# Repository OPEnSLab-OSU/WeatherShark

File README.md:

# WeatherShark

Links via Fusion to CAD files to 3D print

Hanging rod: http://a360.co/2F3G7Bz

Crossbar: http://a360.co/2F3G7Bz

Bearing Hanger: http://a360.co/2EYjwWZ

Fiber Clamp: http://a360.co/2FCrSVv - the new version of this needs to be refined a bit to get a good latch on the fiber

Ventilator with Turbine Rod: http://a360.co/2EYo6IR

Body + Bottom Plate: http://a360.co/2EXwTed

Note: Currently missing in the documentation: the WeatherShark board should have a 100 kOhm resistor from the RTC INT Pin to VCC.

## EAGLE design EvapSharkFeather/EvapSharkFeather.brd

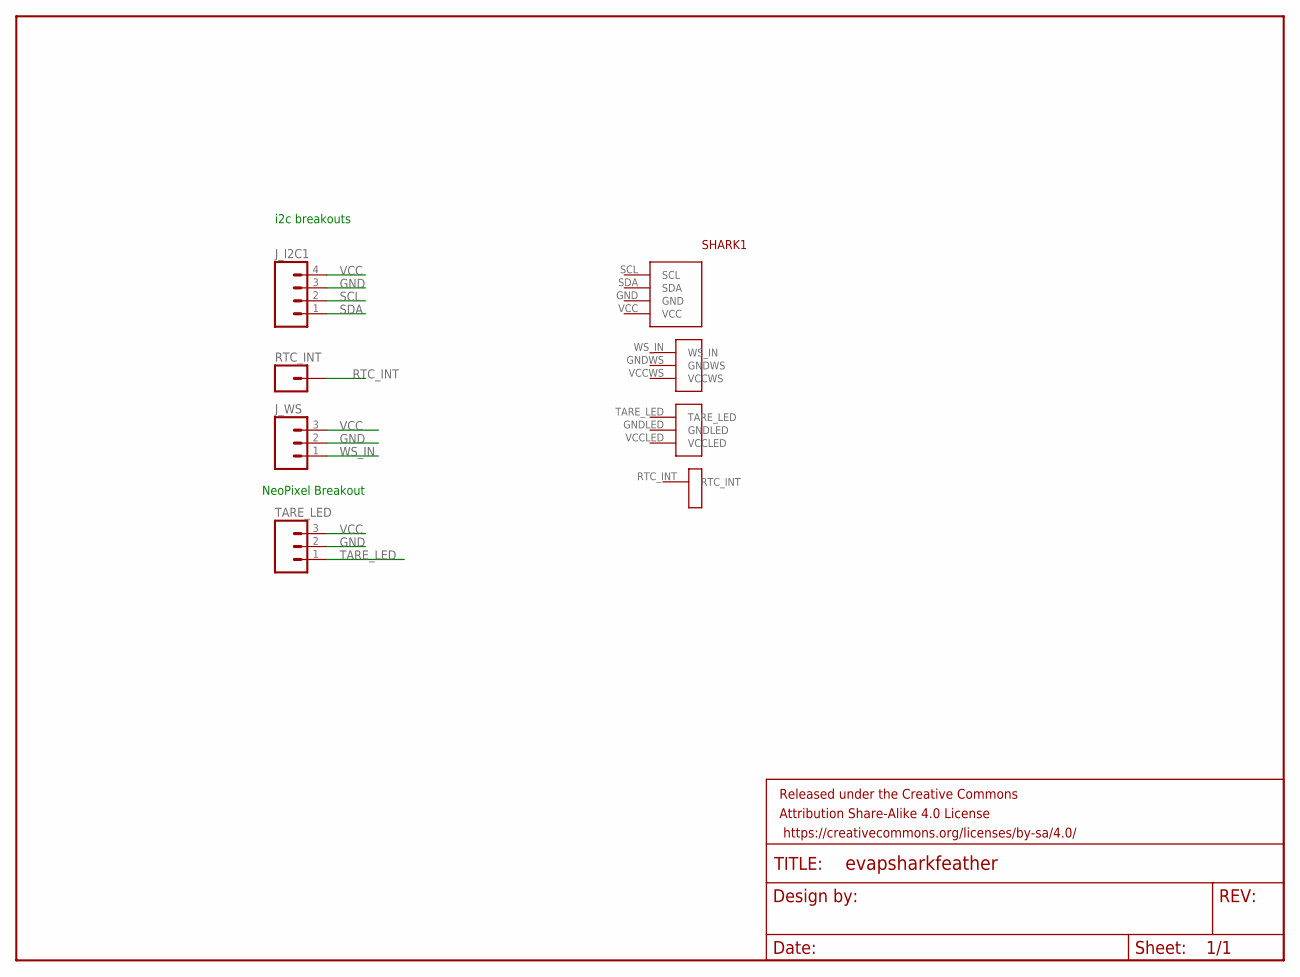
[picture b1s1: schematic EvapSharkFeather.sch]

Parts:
FRAME1: FRAME-LETTER; CREATIVE_COMMONS
J_I2C1: M04PTH; 1X04
J_WS: M03PTH; 1X03
RTC_INT: M01PTH; 1X01
SHARK1: EVAPSHARK
TARE_LED: M03PTH; 1X03

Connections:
GND: J_I2C1.3, J_WS.2, SHARK1.GND, TARE_LED.2
GNDLED: SHARK1.GNDLED
GNDWS: SHARK1.GNDWS
RTC_INT: RTC_INT.1
SCL: J_I2C1.2
SDA: J_I2C1.1
TARE_LED: TARE_LED.1
VCC: J_I2C1.4, J_WS.3, SHARK1.VCC, TARE_LED.3
VCCLED: SHARK1.VCCLED
VCCWS: SHARK1.VCCWS
WS_IN: J_WS.1

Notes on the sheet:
i2c breakouts
NeoPixel Breakout

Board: 2 copper layers, 17 parts (0 on the bottom side), 2 nets, no tracks yet.

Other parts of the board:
BMP1: ADAFRUITBMP280
BNO1: ADAFRUITBNO055
DS1: ADAFRUITDS3231
J1: MOLEX-1X6
NEO1: ADAFRUITNEOPIXELBREAKOUT
R1, R2, R3, R4, R5: AXIAL-0.3
U1: DIP08-KIT

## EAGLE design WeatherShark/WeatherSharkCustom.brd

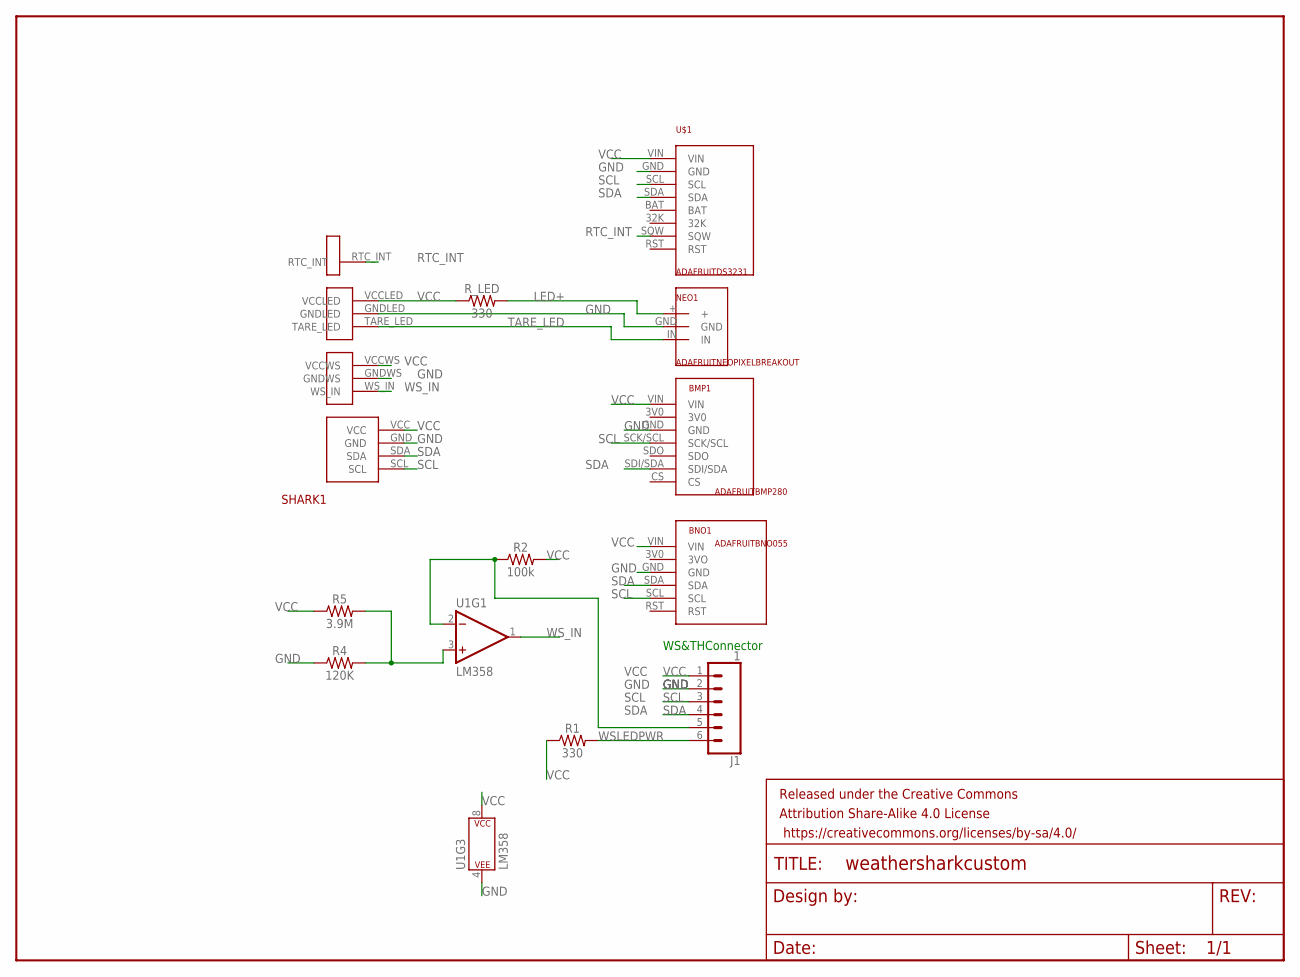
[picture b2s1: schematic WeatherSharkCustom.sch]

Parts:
BMP1: ADAFRUITBMP280
BNO1: ADAFRUITBNO055
FRAME1: FRAME-LETTER; CREATIVE_COMMONS
J1: 1; MOLEX-1X6
NEO1: ADAFRUITNEOPIXELBREAKOUT
R1: 330; AXIAL-0.3
R2: 100k; AXIAL-0.3
R4: 120K; AXIAL-0.3
R5: 3.9M; AXIAL-0.3
R_LED: 330; AXIAL-0.3
SHARK1: EVAPSHARK
U1: LM358; DIP08-KIT
U$1: ADAFRUITDS3231

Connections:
COMP: R4.P$2 (2), R5.P$2 (2), U1.3 (+IN)
GND: BMP1.GND, BNO1.GND, J1.2, NEO1.GND, R4.P$1 (1), SHARK1.GND, SHARK1.GNDLED, SHARK1.GNDWS, U1.4 (P$V-), U$1.GND
LED+: NEO1.+, R_LED.P$2 (2)
RTC_INT: SHARK1.RTC_INT, U$1.SQW
SCL: BMP1.SCK/SCL, BNO1.SCL, J1.3, SHARK1.SCL, U$1.SCL
SDA: BMP1.SDI/SDA, BNO1.SDA, J1.4, SHARK1.SDA, U$1.SDA
TARE_LED: NEO1.IN, SHARK1.TARE_LED
VCC: BMP1.VIN, BNO1.VIN, J1.1, R1.P$1 (1), R2.P$2 (2), R5.P$1 (1), R_LED.P$1 (1), SHARK1.VCC, SHARK1.VCCLED, SHARK1.VCCWS, U1.8 (P$V+), U$1.VIN
WSLEDPWR: J1.6, R1.P$2 (2)
WSSIGNAL: J1.5, R2.P$1 (1), U1.2 (-IN)
WS_IN: SHARK1.WS_IN, U1.1 (OUT)

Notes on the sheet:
WS&THConnector

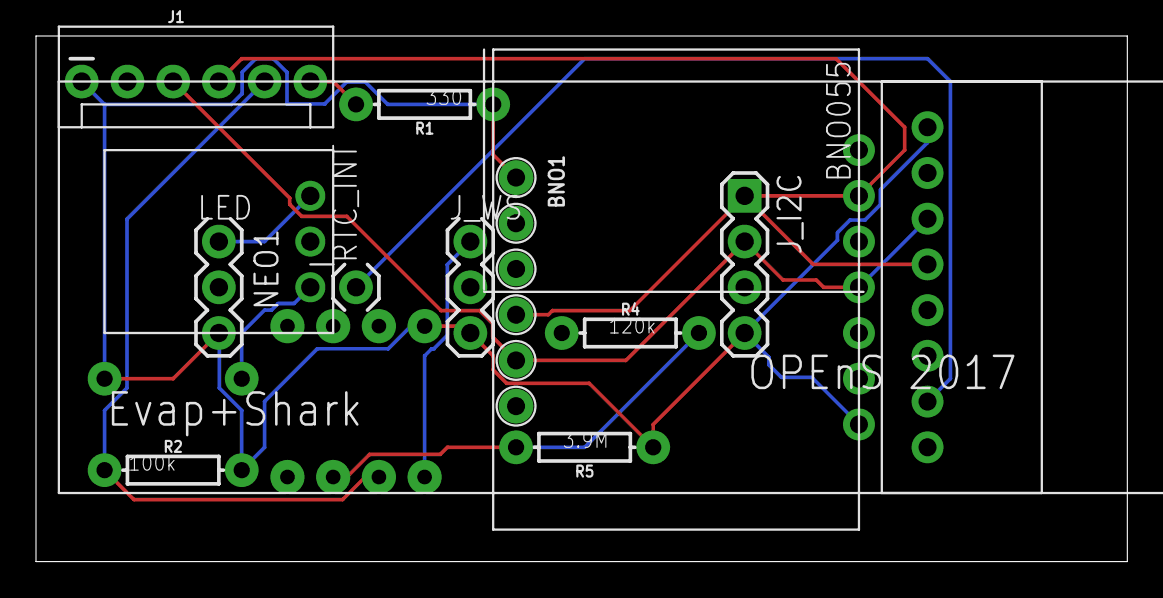
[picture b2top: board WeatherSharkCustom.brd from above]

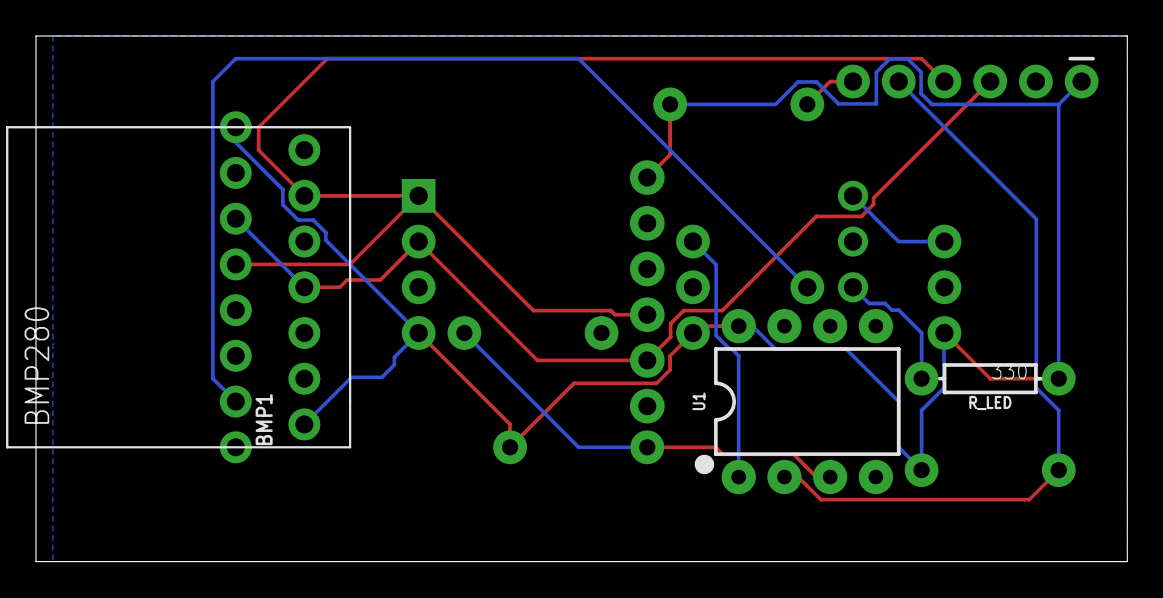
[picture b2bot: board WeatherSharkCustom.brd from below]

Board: 2 copper layers, 60.6 x 29.2 mm, 13 parts (3 on the bottom side), 11 nets.

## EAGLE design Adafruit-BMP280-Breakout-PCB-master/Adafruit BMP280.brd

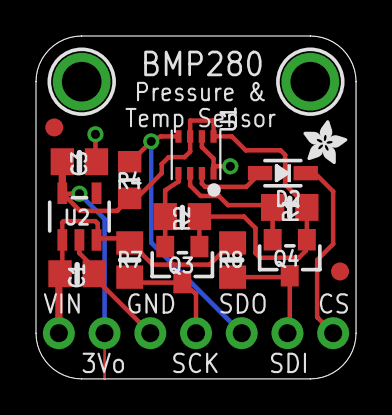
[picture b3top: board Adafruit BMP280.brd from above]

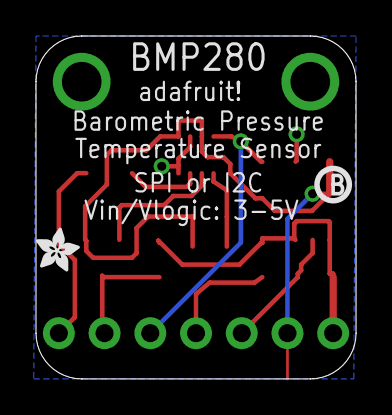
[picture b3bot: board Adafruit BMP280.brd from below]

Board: 2 copper layers, 17.8 x 19.1 mm, 20 parts (2 on the bottom side), 10 nets.

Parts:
C1, C3: 10uF; 0805-NO
D2: 1N4148; SOD-323
JP2: 1X07_ROUND_70
Q3, Q4: BSS138; SOT23-WIDE
R1, R2, R7, R8: 10K; 0805-NO
R4: 10K; _0805MP
U1: BME280
U2: MIC5225-3.3; SOT23-5
U$2, U$6: ADAFRUIT_2.5MM
U$5, U$15: FIDUCIAL""; FIDUCIAL_1MM
U$7, U$8: MOUNTINGHOLE2.0; MOUNTINGHOLE_2.0_PLATED
U$20: PCBFEAT-REV-040

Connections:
3.3V: C3.1, JP2.2, Q3.1, Q4.1, R1.2, R2.2, R4.2, U1.6, U1.8, U2.5
5.0V: C1.1, JP2.1, R7.2, R8.2, U2.1, U2.3
CS_3V: D2.A, U1.2
CS_5V: D2.C, JP2.7
GND: C1.2, C3.2, JP2.3, U1.1, U1.7, U2.2
SCK/SCL_5V: JP2.4, Q3.3, R7.1
SCK_3V: Q3.2, R2.1, U1.4
SDI/SDA_5V: JP2.6, Q4.3, R8.1
SDI_3V: Q4.2, R1.1, U1.3
SDO/ADR_3V: JP2.5, R4.1, U1.5

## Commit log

2017-12-05 Add existing file
2018-03-06 Added links for CAD files for parts to 3D print
    Also added note about missing resistor
2018-03-06 Formatting
2018-03-06 Added BOM and AGU poster

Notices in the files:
parts and their libraries:
SparkFun-Connectors: Licensing: Creative Commons ShareAlike 4.0 International - https://creativecommons.org/licenses/by-sa/4.0
SparkFun-Aesthetics: Released under the Creative Commons Attribution Share-Alike 4.0 License
SparkFun-Aesthetics: https://creativecommons.org/licenses/by-sa/4.0
